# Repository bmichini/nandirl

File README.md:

# nandirl
Project documentation can be found at [bmichini.github.io/nandirl](https://bmichini.github.io/nandirl/) 

## License
The hardware design files and software tools found in this repository are open source and released under the [Creative Commons Attribution-ShareAlike 4.0 International License](http://creativecommons.org/licenses/by-sa/4.0/) (CC BY-SA 4.0)

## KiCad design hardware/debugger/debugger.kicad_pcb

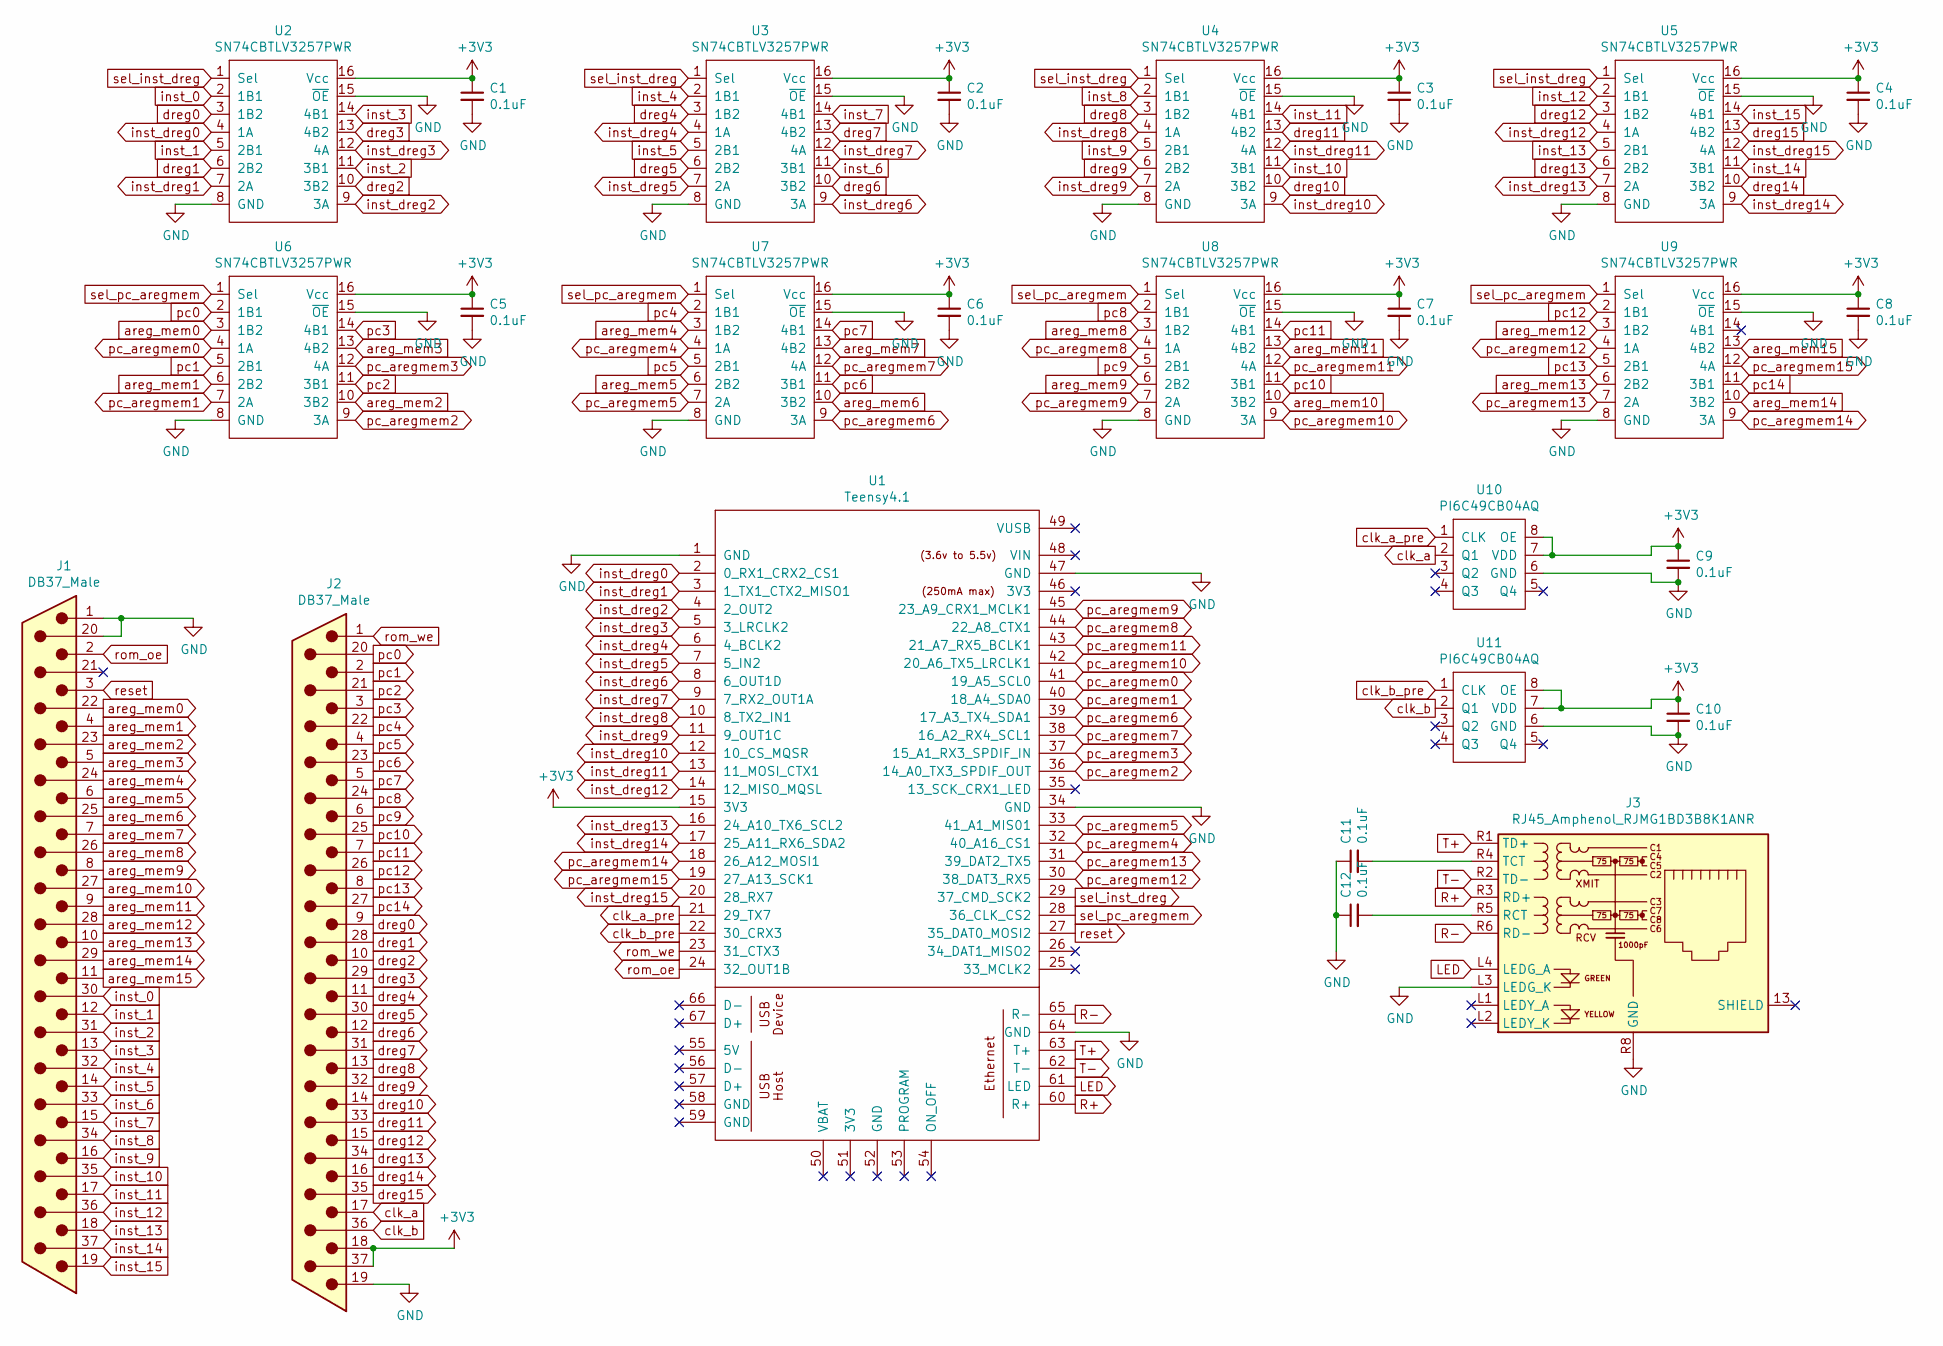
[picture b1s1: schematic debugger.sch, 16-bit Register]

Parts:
C1, C2, C3, C4, C5, C6, C7, C8, C9, C10, C11, C12: 0.1uF; C_1206_3216Metric; Digikey PN 399-C1206C104K5RAC7800CT-ND
J1, J2: DB37_Male; DSUB-37_Male_Horizontal_P2.77x2.84mm_EdgePinOffset7.70mm_Ho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; Digikey PN AE10986-ND
J3: RJ45_Amphenol_RJMG1BD3B8K1ANR; Digikey PN RJMG1BD3B8K1ANR-ND
U1: Teensy4.1; Teensy41
U2, U3, U4, U5, U6, U7, U8, U9: SN74CBTLV3257PWR; TSSOP-16_4.4x5mm_P0.65mm; Digikey PN 296-9138-1-ND
U10, U11: PI6C49CB04AQ; SOIC-8_3.9x4.9mm_P1.27mm; Digikey PN 31-PI6C49CB04AQ2WEXCT-ND

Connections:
+3V3: C1.1, C2.1, C3.1, C4.1, C5.1, C6.1, C7.1, C8.1, C9.1, C10.1, J2.18, J2.37, U1.15 (3V3), U2.16 (Vcc), U3.16 (Vcc), U4.16 (Vcc), U5.16 (Vcc), U6.16 (Vcc), U7.16 (Vcc), U8.16 (Vcc), U9.16 (Vcc), U10.7 (VDD), U10.8 (OE), U11.7 (VDD), U11.8 (OE)
GND: C1.2, C2.2, C3.2, C4.2, C5.2, C6.2, C7.2, C8.2, C9.2, C10.2, C11.1, C12.1, J1.1, J1.20, J2.19, J3.L3 (LEDG_K), J3.R8 (GND), U1.1 (GND), U1.34 (GND), U1.47 (GND), U1.64 (GND), U2.8 (GND), U2.15 (~OE), U3.8 (GND), U3.15 (~OE), U4.8 (GND), U4.15 (~OE), U5.8 (GND), U5.15 (~OE), U6.8 (GND), U6.15 (~OE), U7.8 (GND), U7.15 (~OE), U8.8 (GND), U8.15 (~OE), U9.8 (GND), U9.15 (~OE), U10.6 (GND), U11.6 (GND)
LED: J3.L4 (LEDG_A), U1.61 (LED)
unnamed: C11.2, J3.R4 (TCT)
unnamed: C12.2, J3.R5 (RCT)
R+: J3.R3 (RD+), U1.60 (R+)
R-: J3.R6 (RD-), U1.65 (R-)
T+: J3.R1 (TD+), U1.63 (T+)
T-: J3.R2 (TD-), U1.62 (T-)
areg_mem0: J1.22, U6.3 (1B2)
areg_mem1: J1.4, U6.6 (2B2)
areg_mem2: J1.23, U6.10 (3B2)
areg_mem3: J1.5, U6.13 (4B2)
areg_mem4: J1.24, U7.3 (1B2)
areg_mem5: J1.6, U7.6 (2B2)
areg_mem6: J1.25, U7.10 (3B2)
areg_mem7: J1.7, U7.13 (4B2)
areg_mem8: J1.26, U8.3 (1B2)
areg_mem9: J1.8, U8.6 (2B2)
areg_mem10: J1.27, U8.10 (3B2)
areg_mem11: J1.9, U8.13 (4B2)
areg_mem12: J1.28, U9.3 (1B2)
areg_mem13: J1.10, U9.6 (2B2)
areg_mem14: J1.29, U9.10 (3B2)
areg_mem15: J1.11, U9.13 (4B2)
clk_a: J2.17, U10.2 (Q1)
clk_a_pre: U1.21 (29_TX7), U10.1 (CLK)
clk_b: J2.36, U11.2 (Q1)
clk_b_pre: U1.22 (30_CRX3), U11.1 (CLK)
dreg0: J2.9, U2.3 (1B2)
dreg1: J2.28, U2.6 (2B2)
dreg2: J2.10, U2.10 (3B2)
dreg3: J2.29, U2.13 (4B2)
dreg4: J2.11, U3.3 (1B2)
dreg5: J2.30, U3.6 (2B2)
dreg6: J2.12, U3.10 (3B2)
dreg7: J2.31, U3.13 (4B2)
dreg8: J2.13, U4.3 (1B2)
dreg9: J2.32, U4.6 (2B2)
dreg10: J2.14, U4.10 (3B2)
dreg11: J2.33, U4.13 (4B2)
dreg12: J2.15, U5.3 (1B2)
dreg13: J2.34, U5.6 (2B2)
dreg14: J2.16, U5.10 (3B2)
dreg15: J2.35, U5.13 (4B2)
inst_0: J1.30, U2.2 (1B1)
inst_1: J1.12, U2.5 (2B1)
inst_2: J1.31, U2.11 (3B1)
inst_3: J1.13, U2.14 (4B1)
inst_4: J1.32, U3.2 (1B1)
inst_5: J1.14, U3.5 (2B1)
inst_6: J1.33, U3.11 (3B1)
inst_7: J1.15, U3.14 (4B1)
inst_8: J1.34, U4.2 (1B1)
inst_9: J1.16, U4.5 (2B1)
inst_10: J1.35, U4.11 (3B1)
inst_11: J1.17, U4.14 (4B1)
inst_12: J1.36, U5.2 (1B1)
inst_13: J1.18, U5.5 (2B1)
inst_14: J1.37, U5.11 (3B1)
inst_15: J1.19, U5.14 (4B1)
inst_dreg0: U1.2 (0_RX1_CRX2_CS1), U2.4 (1A)
inst_dreg1: U1.3 (1_TX1_CTX2_MISO1), U2.7 (2A)
inst_dreg2: U1.4 (2_OUT2), U2.9 (3A)
inst_dreg3: U1.5 (3_LRCLK2), U2.12 (4A)
inst_dreg4: U1.6 (4_BCLK2), U3.4 (1A)
inst_dreg5: U1.7 (5_IN2), U3.7 (2A)
inst_dreg6: U1.8 (6_OUT1D), U3.9 (3A)
inst_dreg7: U1.9 (7_RX2_OUT1A), U3.12 (4A)
inst_dreg8: U1.10 (8_TX2_IN1), U4.4 (1A)
inst_dreg9: U1.11 (9_OUT1C), U4.7 (2A)
inst_dreg10: U1.12 (10_CS_MQSR), U4.9 (3A)
inst_dreg11: U1.13 (11_MOSI_CTX1), U4.12 (4A)
inst_dreg12: U1.14 (12_MISO_MQSL), U5.4 (1A)
inst_dreg13: U1.16 (24_A10_TX6_SCL2), U5.7 (2A)
inst_dreg14: U1.17 (25_A11_RX6_SDA2), U5.9 (3A)
inst_dreg15: U1.20 (28_RX7), U5.12 (4A)
pc0: J2.20, U6.2 (1B1)
pc1: J2.2, U6.5 (2B1)
pc2: J2.21, U6.11 (3B1)
pc3: J2.3, U6.14 (4B1)
pc4: J2.22, U7.2 (1B1)
pc5: J2.4, U7.5 (2B1)
pc6: J2.23, U7.11 (3B1)
pc7: J2.5, U7.14 (4B1)
pc8: J2.24, U8.2 (1B1)
pc9: J2.6, U8.5 (2B1)
pc10: J2.25, U8.11 (3B1)
pc11: J2.7, U8.14 (4B1)
pc12: J2.26, U9.2 (1B1)
pc13: J2.8, U9.5 (2B1)
pc14: J2.27, U9.11 (3B1)
pc_aregmem0: U1.41 (19_A5_SCL0), U6.4 (1A)
pc_aregmem1: U1.40 (18_A4_SDA0), U6.7 (2A)
pc_aregmem2: U1.36 (14_A0_TX3_SPDIF_OUT), U6.9 (3A)
pc_aregmem3: U1.37 (15_A1_RX3_SPDIF_IN), U6.12 (4A)
pc_aregmem4: U1.32 (40_A16_CS1), U7.4 (1A)
pc_aregmem5: U1.33 (41_A1_MIS01), U7.7 (2A)
pc_aregmem6: U1.39 (17_A3_TX4_SDA1), U7.9 (3A)
pc_aregmem7: U1.38 (16_A2_RX4_SCL1), U7.12 (4A)
pc_aregmem8: U1.44 (22_A8_CTX1), U8.4 (1A)
pc_aregmem9: U1.45 (23_A9_CRX1_MCLK1), U8.7 (2A)
pc_aregmem10: U1.42 (20_A6_TX5_LRCLK1), U8.9 (3A)
pc_aregmem11: U1.43 (21_A7_RX5_BCLK1), U8.12 (4A)
pc_aregmem12: U1.30 (38_DAT3_RX5), U9.4 (1A)
pc_aregmem13: U1.31 (39_DAT2_TX5), U9.7 (2A)
pc_aregmem14: U1.18 (26_A12_MOSI1), U9.9 (3A)
pc_aregmem15: U1.19 (27_A13_SCK1), U9.12 (4A)
reset: J1.3, U1.27 (35_DAT0_MOSI2)
rom_oe: J1.2, U1.24 (32_OUT1B)
rom_we: J2.1, U1.23 (31_CTX3)
sel_inst_dreg: U1.29 (37_CMD_SCK2), U2.1 (Sel), U3.1 (Sel), U4.1 (Sel), U5.1 (Sel)
sel_pc_aregmem: U1.28 (36_CLK_CS2), U6.1 (Sel), U7.1 (Sel), U8.1 (Sel), U9.1 (Sel)

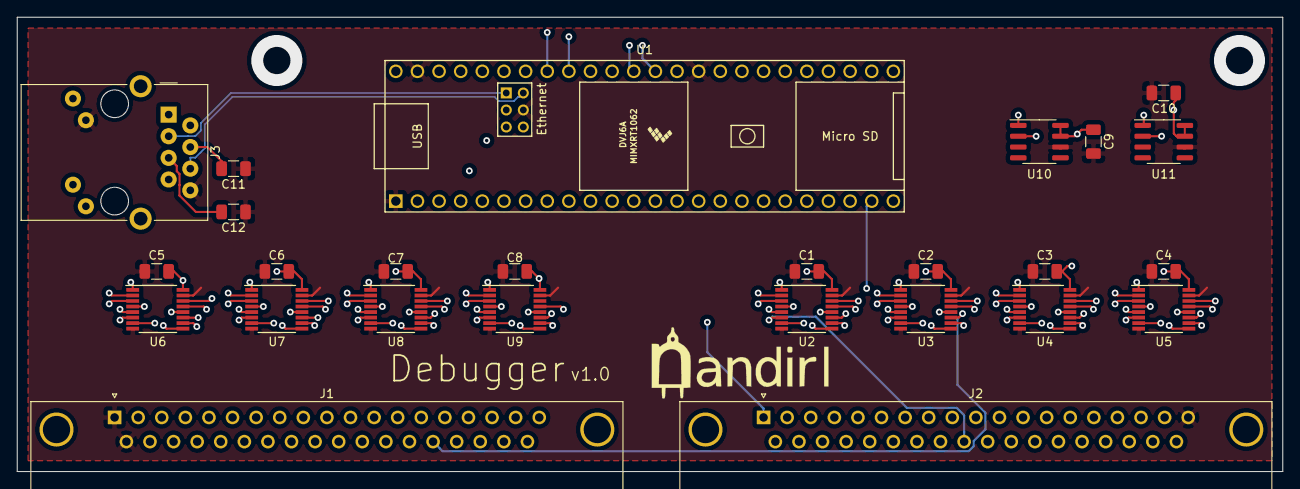
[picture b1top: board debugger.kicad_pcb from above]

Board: 4 copper layers, 148.6 x 53.3 mm, 26 parts (0 on the bottom side), 113 nets.

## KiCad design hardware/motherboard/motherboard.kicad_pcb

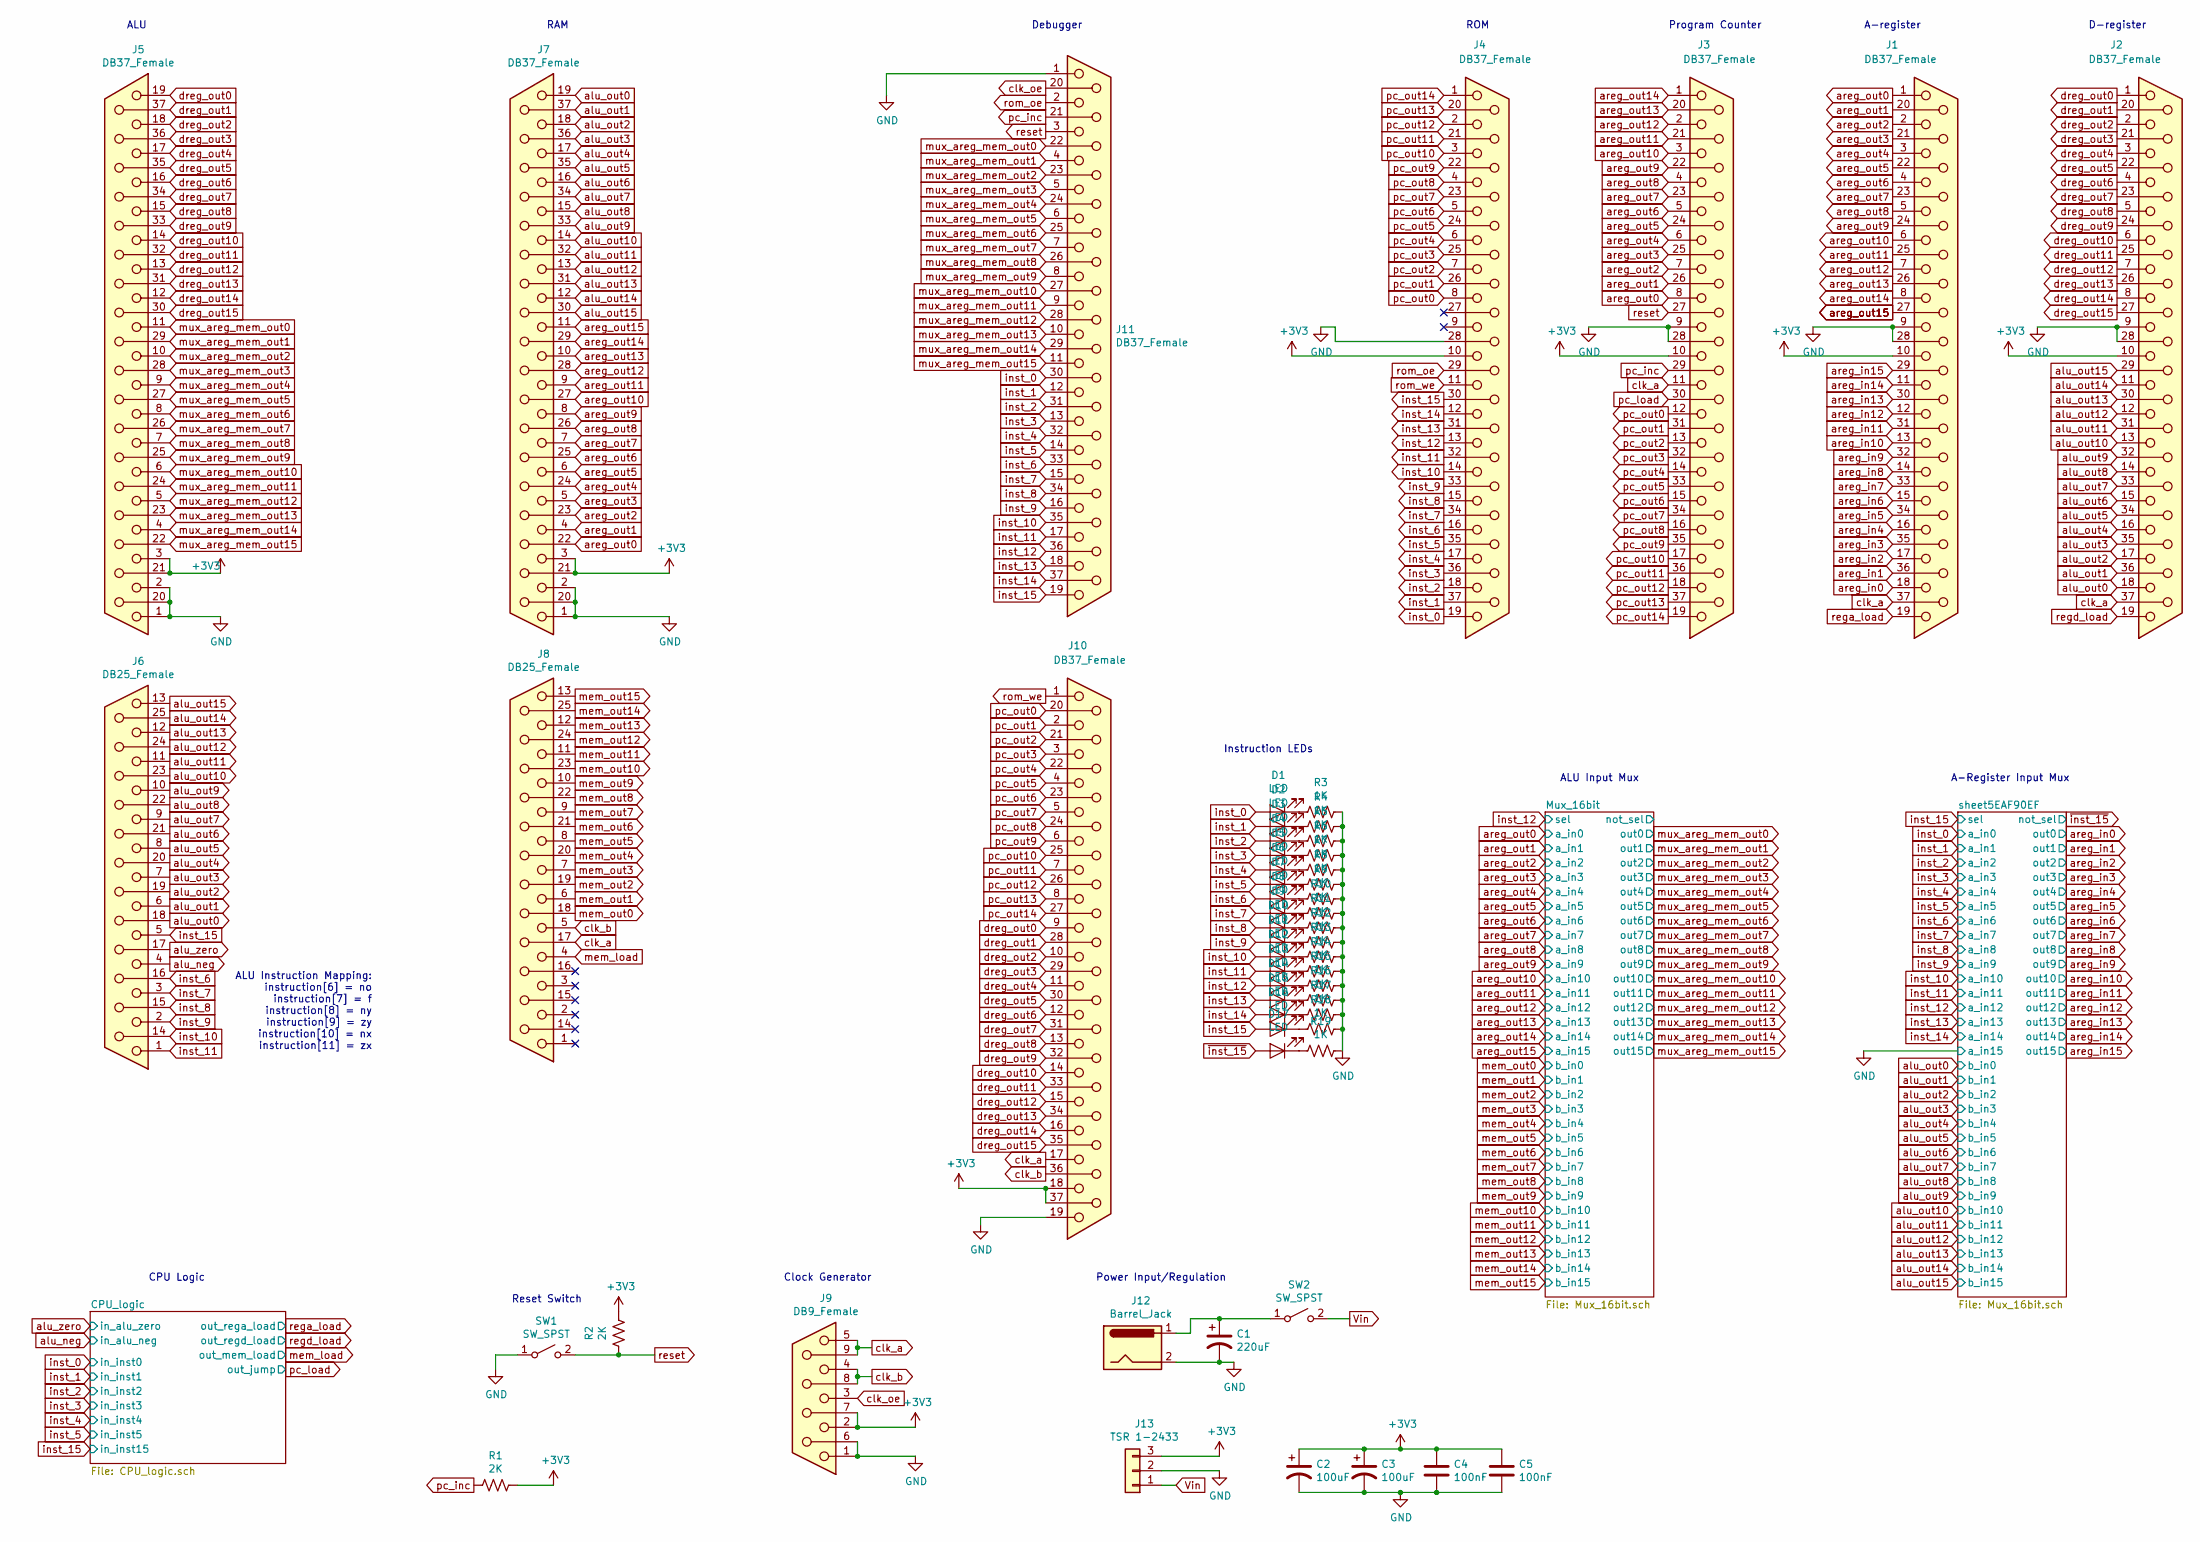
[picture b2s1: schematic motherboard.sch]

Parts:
C1: 220uF; CP_Radial_D10.0mm_P5.00mm; Digikey PN P5183-ND
C2, C3: 100uF; CP_Radial_D8.0mm_P2.50mm; Digikey PN P15797CT-ND
C4, C5: 100nF; C_Disc_D6.0mm_W2.5mm_P5.00mm; Digikey PN BC5229CT-ND
D1, D2, D3, D4, D5, D6, D7, D8, D9, D10, D11, D12, D13, D14, D15, D16, D17: LED; LED_1206_3216Metric; Digikey PN 516-1436-1-ND
J1, J2, J3, J4, J5, J7, J10, J11: DB37_Female; DSUB-37_Female_Horizontal_P2.77x2.84mm_EdgePinOffset7.70mm_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; Digikey PN AE10941-ND
J6, J8: DB25_Female; DSUB-25_Female_Horizontal_P2.77x2.84mm_EdgePinOffset7.70mm_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; Digikey PN AE10935-ND
J9: DB9_Female; DSUB-9_Female_Horizontal_P2.77x2.84mm_EdgePinOffset7.70mm_H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; Digikey PN AE10921-ND
J12: Barrel_Jack; BarrelJack_CUI_PJ-063AH_Horizontal; Digikey PN CP-063AH-ND
J13: TSR 1-2433; PinHeader_1x03_P2.54mm_Vertical; Digikey PN 1951-2430-ND
R1, R2: 2K; R_1206_3216Metric; Digikey PN P2.0KECT-ND
R3, R4, R5, R6, R7, R8, R9, R10, R11, R12, R13, R14, R15, R16, R17, R18, R19: 1K; R_1206_3216Metric; Digikey PN P1.0KECT-ND
SW1: SW_SPST; SW_SPST_B3S-1000; Digikey PN SW415-ND
SW2: SW_SPST; SPST Toggle Switch; Digikey PN EG4914-ND

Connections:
+3V3: C2.1, C3.1, C4.1, C5.1, J1.10, J2.10, J3.10, J4.10, J5.3, J5.21, J7.3, J7.21, J9.2, J9.7, J10.18, J10.37, J13.3, R1.1, R2.1; also elsewhere on the board
GND: C1.2, C2.2, C3.2, C4.2, C5.2, J1.9, J1.28, J2.9, J2.28, J3.9, J3.28, J4.28, J5.1, J5.2, J5.20, J7.1, J7.2, J7.20, J9.1, J9.6, J10.19, J11.1, J12.2, J13.2, R3.1, R4.1, R5.1, R6.1, R7.1, R8.1, R9.1, R10.1, R11.1, R12.1, R13.1, R14.1, R15.1, R16.1, R17.1, R18.1, R19.1, SW1.1 (A); also elsewhere on the board
unnamed: C1.1, J12.1, SW2.1 (A)
unnamed: D1.1 (K), R3.2
unnamed: D2.1 (K), R4.2
unnamed: D3.1 (K), R5.2
unnamed: D4.1 (K), R6.2
unnamed: D5.1 (K), R7.2
unnamed: D6.1 (K), R8.2
unnamed: D7.1 (K), R9.2
unnamed: D8.1 (K), R10.2
unnamed: D9.1 (K), R11.2
unnamed: D10.1 (K), R12.2
unnamed: D11.1 (K), R13.2
unnamed: D12.1 (K), R14.2
unnamed: D13.1 (K), R15.2
unnamed: D14.1 (K), R16.2
unnamed: D15.1 (K), R17.2
unnamed: D16.1 (K), R18.2
unnamed: D17.1 (K), R19.2
Vin: J13.1, SW2.2 (B)
alu_neg: J6.4; also elsewhere on the board
alu_out0: J2.18, J6.18, J7.19; also elsewhere on the board
alu_out1: J2.36, J6.6, J7.37; also elsewhere on the board
alu_out2: J2.17, J6.19, J7.18; also elsewhere on the board
alu_out3: J2.35, J6.7, J7.36; also elsewhere on the board
alu_out4: J2.16, J6.20, J7.17; also elsewhere on the board
alu_out5: J2.34, J6.8, J7.35; also elsewhere on the board
alu_out6: J2.15, J6.21, J7.16; also elsewhere on the board
alu_out7: J2.33, J6.9, J7.34; also elsewhere on the board
alu_out8: J2.14, J6.22, J7.15; also elsewhere on the board
alu_out9: J2.32, J6.10, J7.33; also elsewhere on the board
alu_out10: J2.13, J6.23, J7.14; also elsewhere on the board
alu_out11: J2.31, J6.11, J7.32; also elsewhere on the board
alu_out12: J2.12, J6.24, J7.13; also elsewhere on the board
alu_out13: J2.30, J6.12, J7.31; also elsewhere on the board
alu_out14: J2.11, J6.25, J7.12; also elsewhere on the board
alu_out15: J2.29, J6.13, J7.30; also elsewhere on the board
alu_zero: J6.17; also elsewhere on the board
areg_in0: J1.18; also elsewhere on the board
areg_in1: J1.36; also elsewhere on the board
areg_in2: J1.17; also elsewhere on the board
areg_in3: J1.35; also elsewhere on the board
areg_in4: J1.16; also elsewhere on the board
areg_in5: J1.34; also elsewhere on the board
areg_in6: J1.15; also elsewhere on the board
areg_in7: J1.33; also elsewhere on the board
areg_in8: J1.14; also elsewhere on the board
areg_in9: J1.32; also elsewhere on the board
areg_in10: J1.13; also elsewhere on the board
areg_in11: J1.31; also elsewhere on the board
areg_in12: J1.12; also elsewhere on the board
areg_in13: J1.30; also elsewhere on the board
areg_in14: J1.11; also elsewhere on the board
areg_in15: J1.29; also elsewhere on the board
areg_out0: J1.1, J3.8, J7.22; also elsewhere on the board
areg_out1: J1.20, J3.26, J7.4; also elsewhere on the board
areg_out2: J1.2, J3.7, J7.23; also elsewhere on the board
areg_out3: J1.21, J3.25, J7.5; also elsewhere on the board
areg_out4: J1.3, J3.6, J7.24; also elsewhere on the board
areg_out5: J1.22, J3.24, J7.6; also elsewhere on the board
areg_out6: J1.4, J3.5, J7.25; also elsewhere on the board
areg_out7: J1.23, J3.23, J7.7; also elsewhere on the board
areg_out8: J1.5, J3.4, J7.26; also elsewhere on the board
areg_out9: J1.24, J3.22, J7.8; also elsewhere on the board
areg_out10: J1.6, J3.3, J7.27; also elsewhere on the board
areg_out11: J1.25, J3.21, J7.9; also elsewhere on the board
areg_out12: J1.7, J3.2, J7.28; also elsewhere on the board
areg_out13: J1.26, J3.20, J7.10; also elsewhere on the board
areg_out14: J1.8, J3.1, J7.29; also elsewhere on the board
areg_out15: J1.27, J7.11; also elsewhere on the board
clk_a: J1.37, J2.37, J3.11, J8.17, J9.5, J9.9, J10.17
clk_b: J8.5, J9.4, J9.8, J10.36
clk_oe: J9.3, J11.20
dreg_out0: J2.1, J5.19, J10.9
dreg_out1: J2.20, J5.37, J10.28
dreg_out2: J2.2, J5.18, J10.10
dreg_out3: J2.21, J5.36, J10.29
dreg_out4: J2.3, J5.17, J10.11
dreg_out5: J2.22, J5.35, J10.30
dreg_out6: J2.4, J5.16, J10.12
dreg_out7: J2.23, J5.34, J10.31
dreg_out8: J2.5, J5.15, J10.13
dreg_out9: J2.24, J5.33, J10.32
dreg_out10: J2.6, J5.14, J10.14
dreg_out11: J2.25, J5.32, J10.33
dreg_out12: J2.7, J5.13, J10.15
dreg_out13: J2.26, J5.31, J10.34
dreg_out14: J2.8, J5.12, J10.16
dreg_out15: J2.27, J5.30, J10.35
inst_0: D1.2 (A), J4.19, J11.30; also elsewhere on the board
inst_1: D2.2 (A), J4.37, J11.12; also elsewhere on the board
inst_2: D3.2 (A), J4.18, J11.31; also elsewhere on the board
inst_3: D4.2 (A), J4.36, J11.13; also elsewhere on the board
inst_4: D5.2 (A), J4.17, J11.32; also elsewhere on the board
inst_5: D6.2 (A), J4.35, J11.14; also elsewhere on the board
inst_6: D7.2 (A), J4.16, J6.16, J11.33; also elsewhere on the board
inst_7: D8.2 (A), J4.34, J6.3, J11.15; also elsewhere on the board
inst_8: D9.2 (A), J4.15, J6.15, J11.34; also elsewhere on the board
inst_9: D10.2 (A), J4.33, J6.2, J11.16; also elsewhere on the board
inst_10: D11.2 (A), J4.14, J6.14, J11.35; also elsewhere on the board
inst_11: D12.2 (A), J4.32, J6.1, J11.17; also elsewhere on the board
inst_12: D13.2 (A), J4.13, J11.36; also elsewhere on the board
inst_13: D14.2 (A), J4.31, J11.18; also elsewhere on the board
inst_14: D15.2 (A), J4.12, J11.37; also elsewhere on the board
inst_15: D16.2 (A), J4.30, J6.5, J11.19; also elsewhere on the board
mem_load: J8.4; also elsewhere on the board
mem_out0: J8.18; also elsewhere on the board
mem_out1: J8.6; also elsewhere on the board
mem_out2: J8.19; also elsewhere on the board
mem_out3: J8.7; also elsewhere on the board
mem_out4: J8.20; also elsewhere on the board
mem_out5: J8.8; also elsewhere on the board
mem_out6: J8.21; also elsewhere on the board
mem_out7: J8.9; also elsewhere on the board
mem_out8: J8.22; also elsewhere on the board
mem_out9: J8.10; also elsewhere on the board
mem_out10: J8.23; also elsewhere on the board
mem_out11: J8.11; also elsewhere on the board
mem_out12: J8.24; also elsewhere on the board
mem_out13: J8.12; also elsewhere on the board
mem_out14: J8.25; also elsewhere on the board
mem_out15: J8.13; also elsewhere on the board
mux_areg_mem_out0: J5.11, J11.22; also elsewhere on the board
mux_areg_mem_out1: J5.29, J11.4; also elsewhere on the board
mux_areg_mem_out2: J5.10, J11.23; also elsewhere on the board
mux_areg_mem_out3: J5.28, J11.5; also elsewhere on the board
mux_areg_mem_out4: J5.9, J11.24; also elsewhere on the board
mux_areg_mem_out5: J5.27, J11.6; also elsewhere on the board
mux_areg_mem_out6: J5.8, J11.25; also elsewhere on the board
mux_areg_mem_out7: J5.26, J11.7; also elsewhere on the board
mux_areg_mem_out8: J5.7, J11.26; also elsewhere on the board
mux_areg_mem_out9: J5.25, J11.8; also elsewhere on the board
mux_areg_mem_out10: J5.6, J11.27; also elsewhere on the board
mux_areg_mem_out11: J5.24, J11.9; also elsewhere on the board
mux_areg_mem_out12: J5.5, J11.28; also elsewhere on the board
mux_areg_mem_out13: J5.23, J11.10; also elsewhere on the board
mux_areg_mem_out14: J5.4, J11.29; also elsewhere on the board
mux_areg_mem_out15: J5.22, J11.11; also elsewhere on the board
pc_inc: J3.29, J11.21, R1.2
pc_load: J3.30; also elsewhere on the board
pc_out0: J3.12, J4.8, J10.20
pc_out1: J3.31, J4.26, J10.2
pc_out2: J3.13, J4.7, J10.21
pc_out3: J3.32, J4.25, J10.3
pc_out4: J3.14, J4.6, J10.22
pc_out5: J3.33, J4.24, J10.4
pc_out6: J3.15, J4.5, J10.23
pc_out7: J3.34, J4.23, J10.5
pc_out8: J3.16, J4.4, J10.24
pc_out9: J3.35, J4.22, J10.6
pc_out10: J3.17, J4.3, J10.25
pc_out11: J3.36, J4.21, J10.7
pc_out12: J3.18, J4.2, J10.26
pc_out13: J3.37, J4.20, J10.8
pc_out14: J3.19, J4.1, J10.27
rega_load: J1.19; also elsewhere on the board
regd_load: J2.19; also elsewhere on the board
reset: J3.27, J11.3, R2.2, SW1.2 (B)
rom_addr15: J4.27
rom_addr16: J4.9
rom_oe: J4.29, J11.2
rom_we: J4.11, J10.1
~inst_15: D17.2 (A); also elsewhere on the board

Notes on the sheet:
D-register
A-register
Program Counter
ROM
ALU
ALU Instruction Mapping: instruction[6] = no instruction[7] = f instruction[8] = ny instruction[9] = zy instruction[10] = nx instruction[11] = zx
RAM
ALU Input Mux
A-Register Input Mux
Clock Generator
CPU Logic
Debugger
Power Input/Regulation
Reset Switch
Instruction LEDs
